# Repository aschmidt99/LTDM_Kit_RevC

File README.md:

# LTDM Kit Rev C

Firmware and hardware assets for a Teensy 4.1 based LTDM (Lorentz Time-Domain Multiplex) kit.

### Programming
Iterate quickly on dsp and string behavior in `Code/LTDM_Kit/render.cpp`, leaving precise timing of sensing and actuating untouched by user.
### Interaction
Map hardware controls (buttons/sliders/pedals) to your algorithm through the UI layer.

## Project Structure

- `Code/LTDM_Kit`: Firmware running on Teensy 4.1
- `Code/Python`: capture, analysis, and Audacity automation scripts
- `Code/LTDM_Kit_Control.maxpat`: a maxpatch for overriding the LTDM Kit physical UI or running LTDM kit main board without UI.
- `Electronics`: KiCad project (schematic and pcb) for PCB design
- `CAD`: mechanical STEP/STL assets for enclosure

## Program and Upload
Firmware can be edited and uploaded to the teensy 4.1 via the Arduino 2.X IDE or from VS code.

### Arduino IDE
To use the Arduino IDE, you will need to [(install the Arduino IDE)](https://support.arduino.cc/hc/en-us/articles/360019833020-Download-and-install-Arduino-IDE). Once installed, download the Teensy Board library by following the instructions [(here)](https://www.pjrc.com/teensy/td_download.html).

After firmware changes are made, make sure the teensy is connected and seen by the dropdown menu in the upper left of the IDE. Use the 'upload' button next to this to flash new firmware.

### Arduino CLI (direct)
If this is your first time connecting from a new machine, run this one-time setup first:

1. Install Arduino CLI.
2. Add the Teensy board index URL.
3. Update board indexes and install the Teensy core.
4. Plug in Teensy 4.1 with a data-capable USB cable.
5. Verify the detected USB port before upload.

Example one-time setup commands:

```bash
# Add PJRC Teensy package index (safe to run again if already present)
arduino-cli config add board_manager.additional_urls https://www.pjrc.com/teensy/package_teensy_index.json

# Refresh indexes and install Teensy core
arduino-cli core update-index
arduino-cli core install teensy:avr

# Confirm Teensy core is installed
arduino-cli core list
```

Check that your Teensy is visible and note its port:

```bash
arduino-cli board list
```

On macOS, Teensy ports commonly look like `/dev/cu.usbmodem*`.

To flash code directly from terminal:

```bash
cd Code/LTDM_Kit
arduino-cli compile --fqbn teensy:avr:teensy41 .
arduino-cli upload --fqbn teensy:avr:teensy41 -p /dev/cu.usbmodemXXXX .
```

### VS Code tasks
To flash firmware from VS code, you can use the premade VS code tasks by using `Cmd+Shift+P` -> `Tasks: Run Task` and select:

- `Teensy: Compile LTDM_Kit`
- `Teensy: Upload LTDM_Kit (prompt port)`
- `Teensy: Upload LTDM_Kit (auto port)`
- `Teensy: Compile + Upload LTDM_Kit (auto port)`

Task definitions live in `.vscode/tasks.json`.

## How the Firmware is Organized

### Essential core files (base firmware)

- `LTDM_Kit.ino`: startup order and top-level loop (`setup()` and `loop()`).
- `flexpwm.cpp` / `flexpwm.h`: hardware timing, ISR, ADC reads, and PWM update path.
- `render.cpp` / `render.h`: per-sample behavior, where algorithm/control logic is authored.
- `ui.cpp` / `ui.h`: physical control scan (buttons/sliders/pedals), LED updates, and serial telemetry printout.
- `channel.h`: per-channel runtime/state struct fields used by ISR and render.
- `context.h`: shared frame context passed into `render()` each sample.
- `pinmap.h`: board pin assignments and hardware routing constants.
- `system_config.h`: global compile-time configuration (sample rate, buffer sizes, PWM resolution).

### Optional or bonus helper modules

These are useful, but not strictly required for a minimal "sense -> render -> actuate" base path.

- `serialctrl.cpp` / `serialctrl.h`: optional host serial override of hardware UI state (used by Max patch control).
- `capture_stream.cpp` / `capture_stream.h`: optional deterministic capture trigger and streaming for measurement scripts.
- `harmonics.cpp` / `harmonics.h`: additive harmonic oscillator bank and zero-crossing pitch tracking.
- `visualAlias.cpp` / `visualAlias.h`: optional visual alias output behavior by plugging a 12V LED strip into one of the channels.
- `SineTable.cpp` / `SineTable.h`: lookup-table sine source used by harmonic/visual helper DSP.
- `debug.h`: compile-time debug print macros (`DEBUG_PRINT`, `DEBUG_PRINTLN`).

At runtime, the flow is:

1. ISR acquires channel state and UI state into `context`.
2. `render(context)` computes output values once per sample.
3. PWM/sense outputs are driven from those computed values.

## Codebase division-of-labor

This codebase intentionally separates three concerns:

1. Real-time infrastructure: sample timing, GPIO/PWM scheduling, ADC/sense capture.
2. Control surface: what knobs/buttons/pedals currently mean.
3. Algorithm: how measured input becomes actuation output.

The design goal is to let you iterate and develop actuation and feedback behavior without destabilizing anything with critical timing, such as the regular periodic sense + actuate loop.

In practice, treat `render.cpp` as your sandbox for algorithmic ideas:

- Feedback shaping
- Noise injection and excitation strategies
- RMS/energy targeting
- Harmonic synthesis
- Cross-channel coupling experiments

## Where to Make Changes

### Audio/actuation behavior

Edit `Code/LTDM_Kit/render.cpp`.

Key entry points:

- `bool renderSetup(LorentzContext *context)` for one-time setup
- `void render(LorentzContext *context)` for per-sample behavior

Useful signals available from `context`:

- `context->ch[0].in`, `context->ch[1].in` (channel's sensed audio input)
- `context->buttons[0]` (button 0-7 are the latching buttons, and 6-15 are the momentary push buttons)
- `context->sliders[0..15]` (slider 0-7 are the potentiometers, 8-15 are the sliders)
- `context->pedals[0..1]` (optionally connect up to 2 expression pedals)

### Button/slider behavior mapping

Edit `Code/LTDM_Kit/ui.cpp` and `Code/LTDM_Kit/render.cpp` together.

How it works:

1. `ui.cpp` scans physical mux inputs and sets UI LED outputs.
2. `render.cpp` assigns meaning to those logical indices.

### Pin assignments

Edit `Code/LTDM_Kit/pinmap.h` only if attaching additional functions to the available GPIOs.

### Render/control behavior (channel 1 focused)

In `Code/LTDM_Kit/render.cpp`:

- Button 0/1 enables channel 1 and 2 output respectively (`enablePin` high/low).
- Button 2 toggles RMS-targeted gain behavior for CH1.
- Button 6 gates CH1 noise injection.
- Button 8 requests capture start while capture is armed.

- Slider 0: CH1 feedback gain (`fbGain`).
- Slider 1: CH1 target RMS.
- Slider 2: noise update rate (acts like coarse smoothing on random term).
- Slider 3: CH1 noise scale.
- Slider 4: harmonic frequency smoothing parameter (`alpha`).
- Sliders 8..15: gains for harmonics 1..8 (`NUM_HARMONICS = 8`).

- Note: Channel 2 currently carries visual-alias pulse output behavior (`renderLEDPulse(...)`) rather than string feedback behavior

### LED/UI feedback

In `Code/LTDM_Kit/ui.cpp`:

- TLC5947 LEDs reflect enable/limit/target and measured RMS states.
- UI scan runs in two-step mux read/write cycles.
- `output()` also prints debug telemetry over serial every ~100 ms (as long as the the python audio capture stream is idle.)

### Serial override mode

`Code/LTDM_Kit/serialctrl.cpp` can override hardware controls via framed serial packets. There is an example max/msp patch ('LTDM_Kit_Control.maxpat') that already has this setup.

- Start marker: `255`
- End marker: `254`
- Payload: mode + 16 sliders + 16 buttons + 2 pedals (34 bytes)

When override is active, incoming values are written directly into the shared UI state arrays.

## Python Tools

The Python tools in `Code/Python` are used for measurement, capture automation, and analysis around the firmware:

- `capture_teensy_plus_interface.py`: Capture audio directly from Teensy (what the teensy 'hears' from the EMF sensing circuitry) and 2 channels of audio from a connected audio interface. Optionally import these files directly to audacity.
- `run_trial.py`: Prompt for trial/profile/duration and launch the capture workflow via named profiles.
- `capture_teensy_stream.py`: Capture Teensy stream only (without interface capture), with optional WAV export.
- `rigol_capture.py`: Run Rigol DS1054Z waveform/screenshot capture and write trial metadata.
- `load_rigol_capture.py`: Load and interactively inspect saved Rigol capture files.
- `rigol_screen.py`: Capture or convert Rigol's screen images.
- `plot_teensy_stream.py`: Plot saved Teensy stream files for quick signal inspection.

If you are starting from scratch, run this script first:

- `Code/Python/run_trial.py`

It prompts for trial and duration, auto-suggests the next trial number, and launches the full capture pipeline with known-good defaults.

Full Python docs:

- `Code/Python/PYTHON_README.md`

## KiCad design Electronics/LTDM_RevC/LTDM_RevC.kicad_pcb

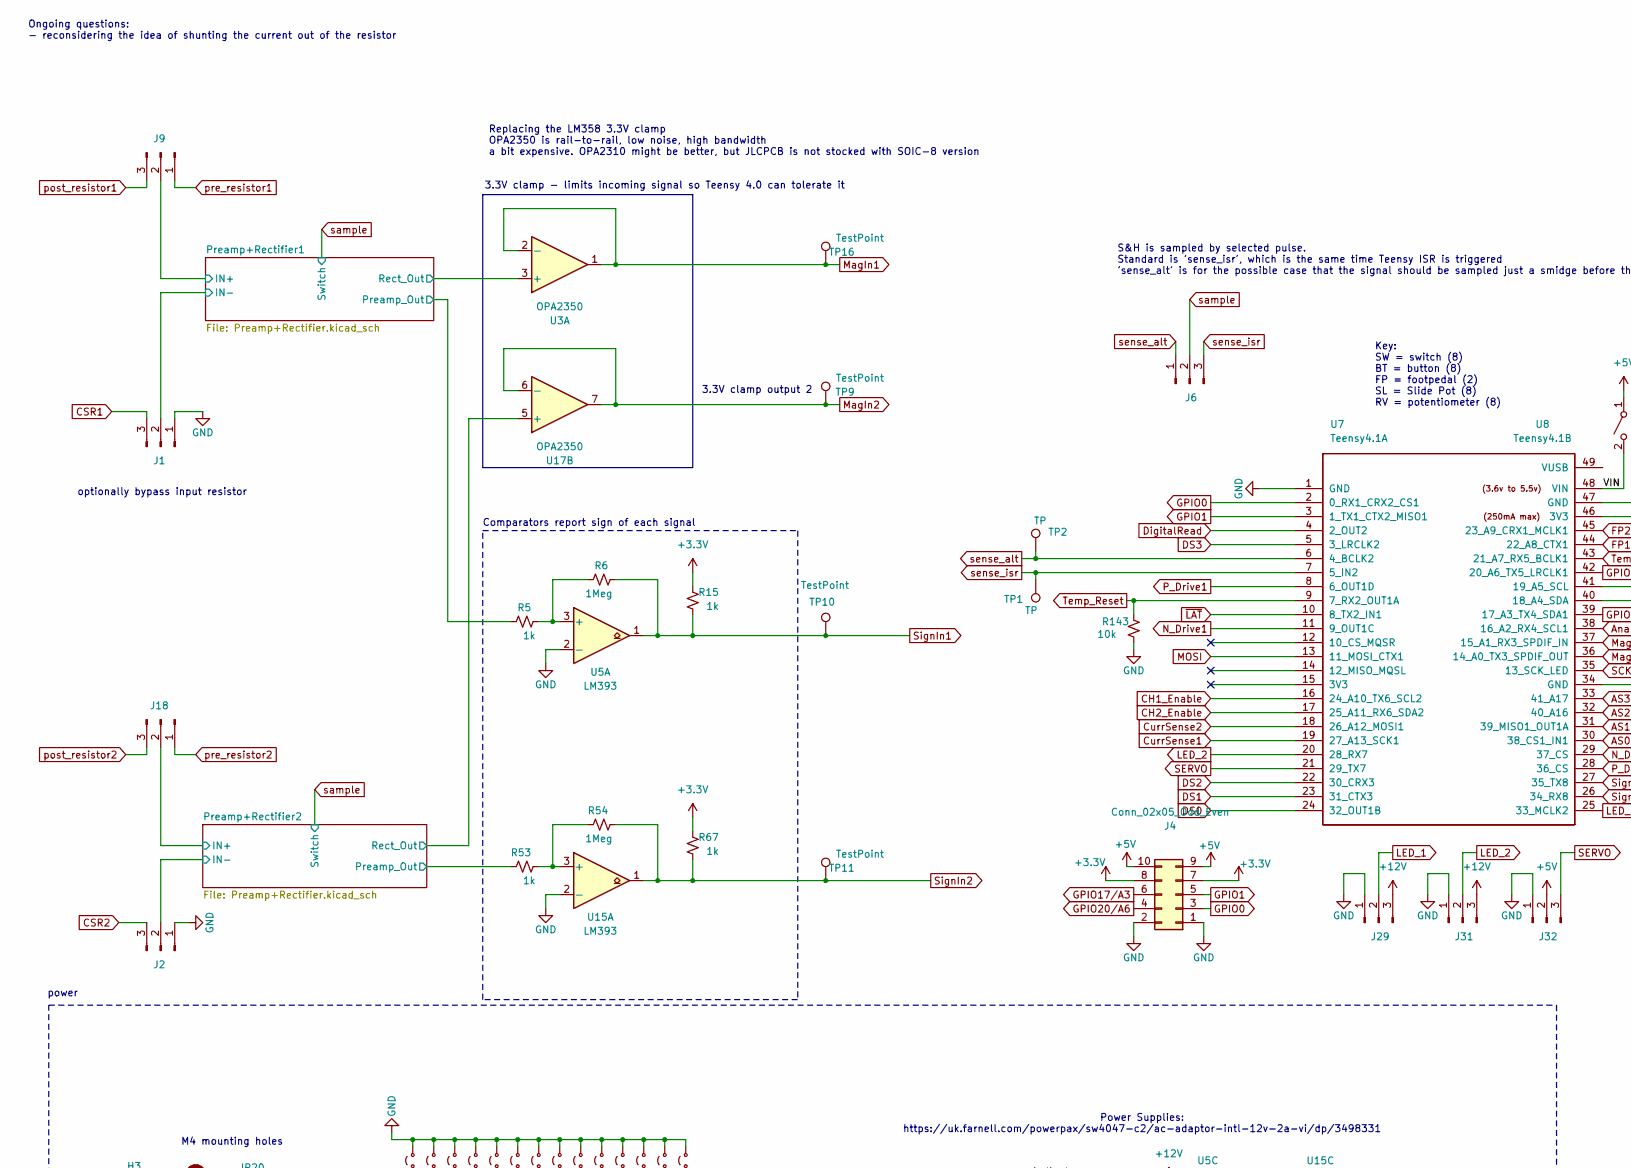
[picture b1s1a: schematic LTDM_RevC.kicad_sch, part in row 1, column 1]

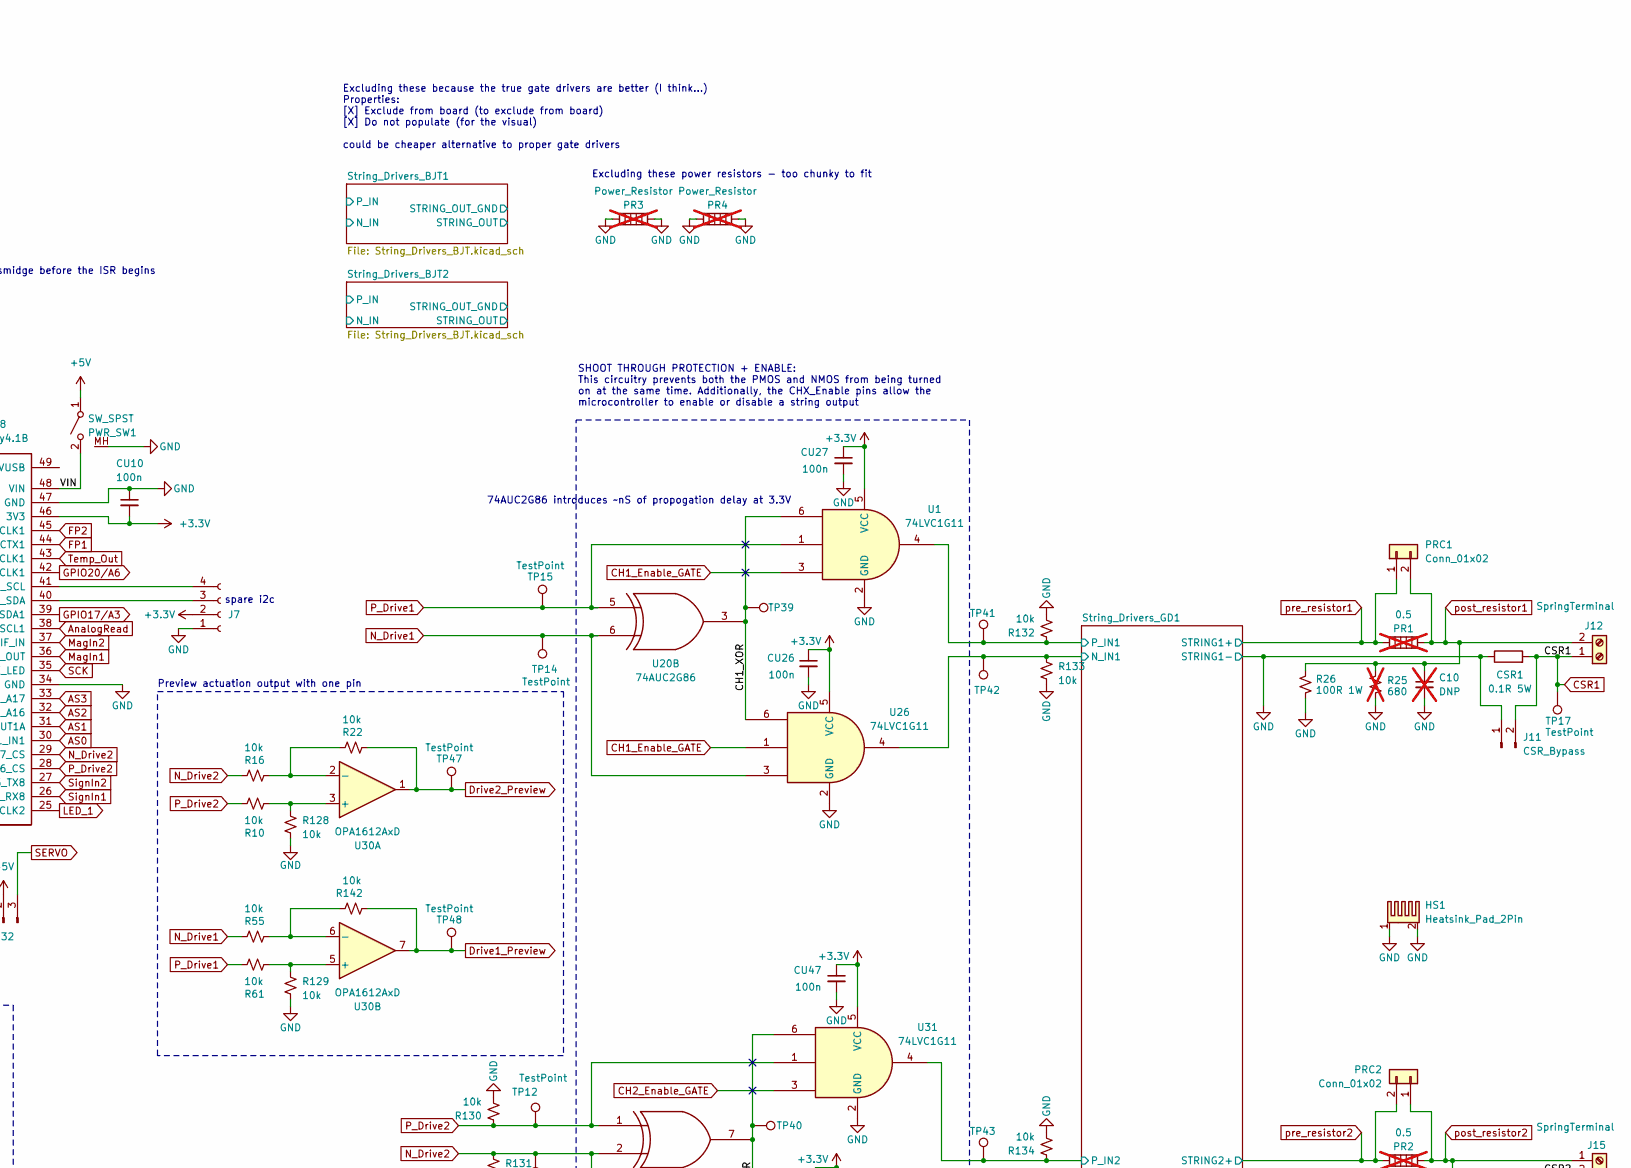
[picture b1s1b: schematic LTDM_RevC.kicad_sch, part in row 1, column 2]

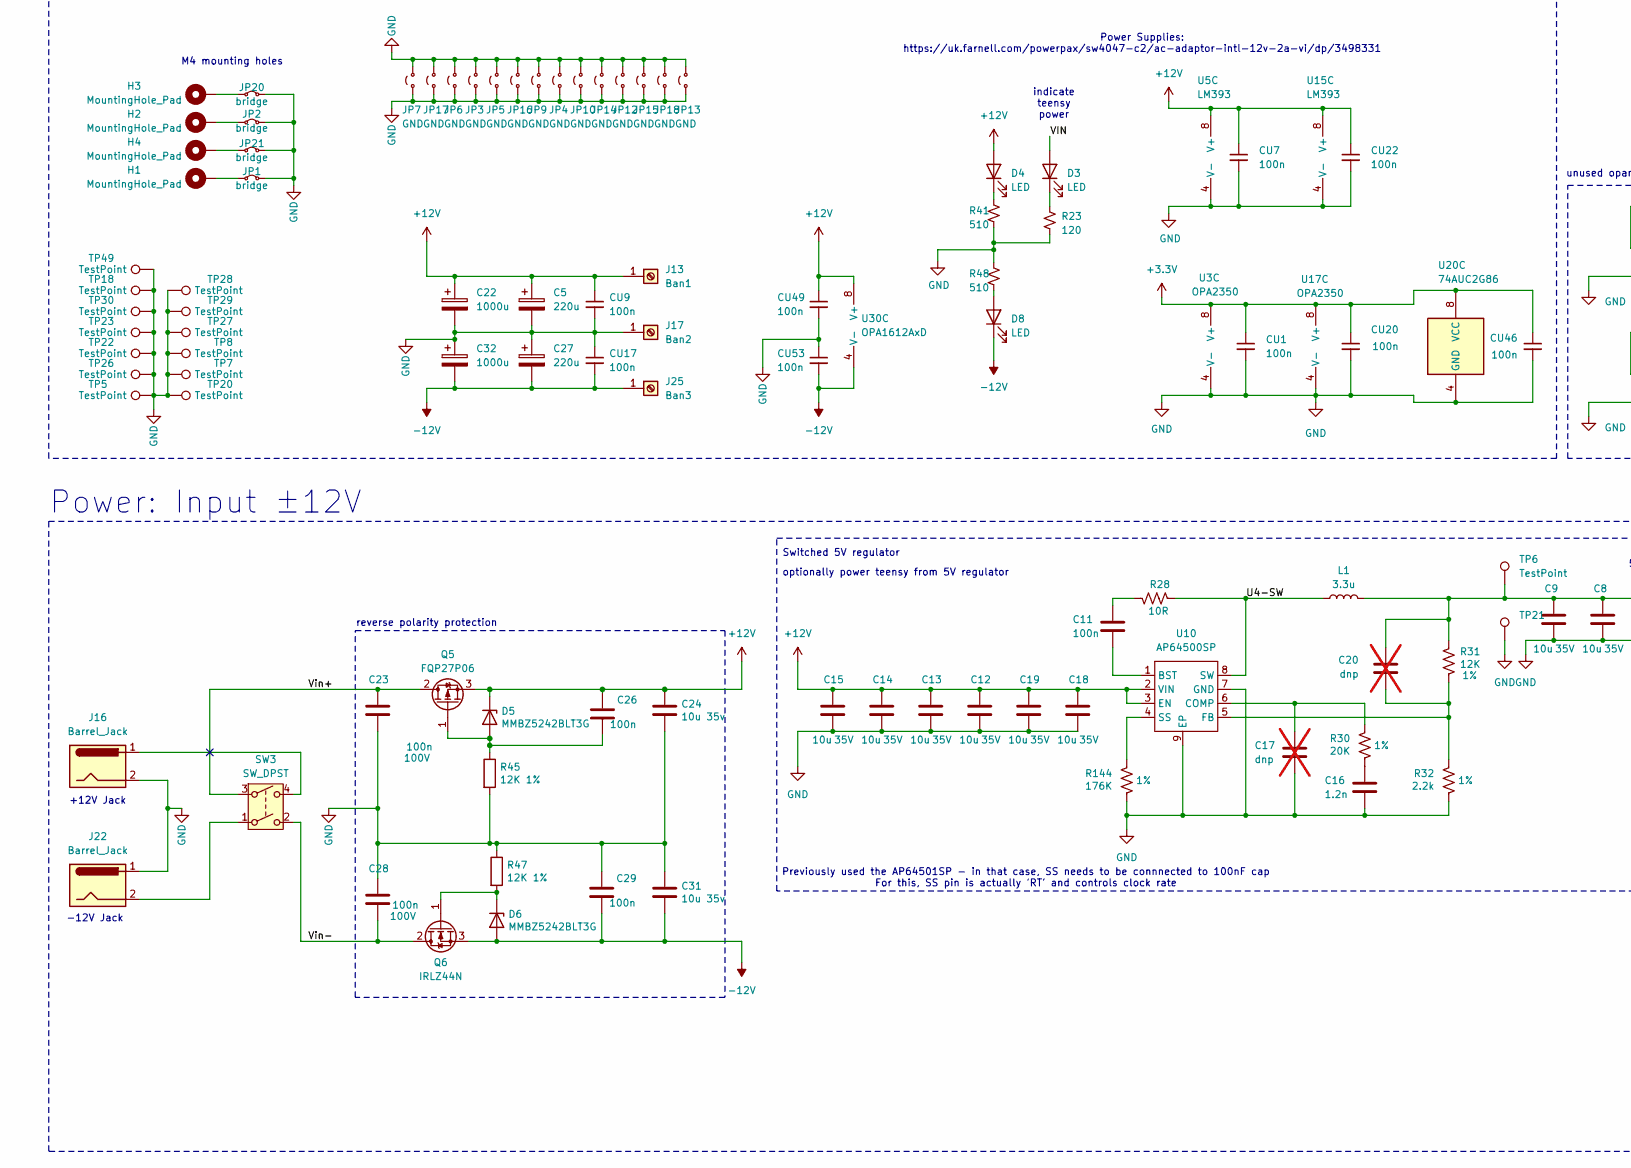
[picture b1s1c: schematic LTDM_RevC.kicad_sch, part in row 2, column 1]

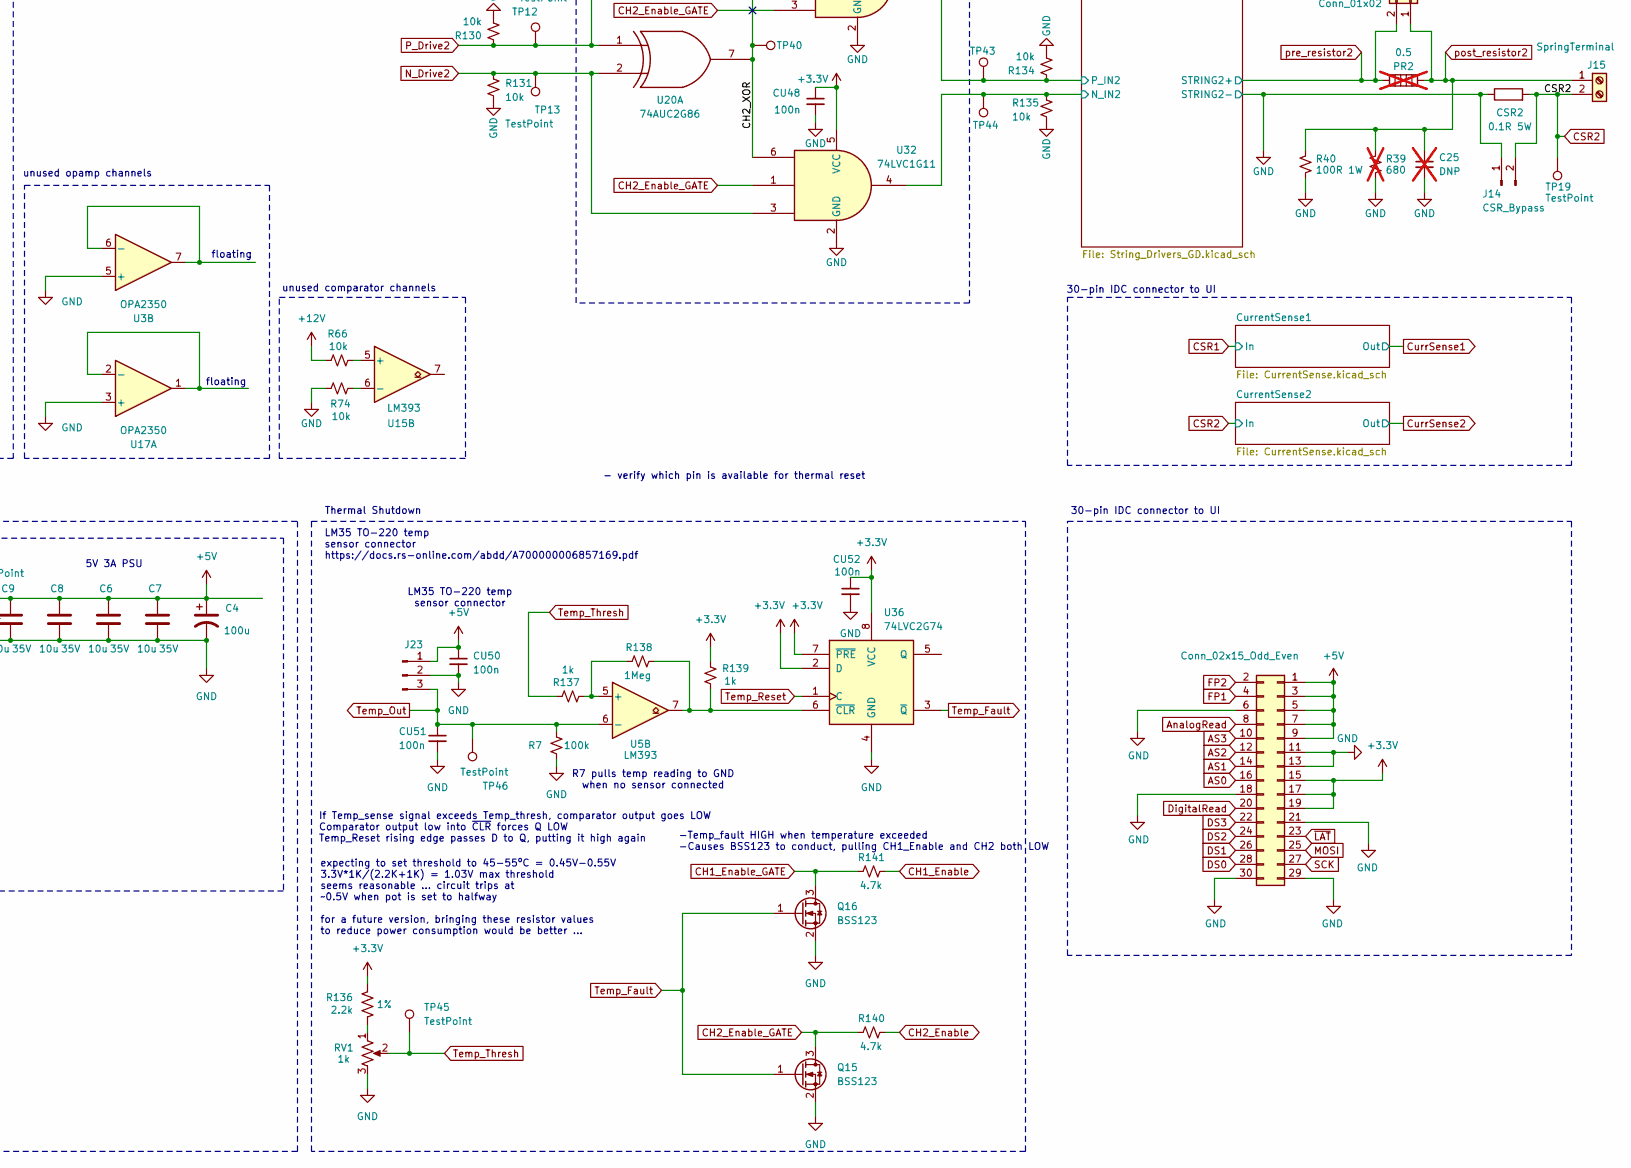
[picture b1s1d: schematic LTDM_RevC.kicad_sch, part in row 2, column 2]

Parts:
C4: 100u; CP_EIA-7343-31_Kemet-D; LCSC C189619
C5, C27: 220u; CP_Radial_D8.0mm_P3.50mm; LCSC C45072
C6, C7, C8, C9: 10u; C_0805_2012Metric; rating 35V; LCSC C117956
C10, C25: DNP; C_Disc_D3.0mm_W1.6mm_P2.50mm; not fitted
C11: 100n; C_0402_1005Metric
C12, C13, C14, C15, C18, C19: 10u; C_0805_2012Metric; rating 35V; LCSC C469541
C16: 1.2n; C_0402_1005Metric
C17, C20: dnp; C_0402_1005Metric; not fitted
C22, C32: 1000u; CP_Radial_D10.0mm_P5.00mm; LCSC C2960265
C23, C28: 100n; C_0402_1005Metric; rating 100V; LCSC C162179
C24, C31: 10u 35v; C_0805_2012Metric; Part Description 10uF 10% or 20% 35V Ceramic Capacitor X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; LCSC C469541
C26, C29: 100n; C_0402_1005Metric; Part Description 0.1uF 10% 16V Ceramic Capacitor X7R 040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; LCSC C92753
CSR1, CSR2: 0.1R 5W; R_4527; LCSC C5127890
CU1, CU7, CU9, CU10, CU17, CU20, CU22, CU26, CU27, CU46, CU47, CU48, CU49, CU50, CU51, CU52, CU53: 100n; C_0603_1608Metric
D3, D4, D8: LED; LED_0603_1608Metric; LCSC C79636
D5, D6: MMBZ5242BLT3G; SOT-23; Part Description Zener Diode 12V 225mW 5% Surface Mount 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; LCSC C896784
H1, H2, H3, H4: MountingHole_Pad; MountingHole_4.3mm_M4_ISO14580_Pad
HS1: Heatsink_Pad_2Pin; Heatsink_Fischer_SK104-STCB_35x13mm__2xDrill3.5mm_ScrewM3
J1, J2, J6, J9, J18, J23, J29, J31, J32: Conn_01x03_Male; PinHeader_1x03_P2.54mm_Vertical; LCSC C2914353
J4: Conn_02x05_Odd_Even; PinHeader_2x05_P2.54mm_Vertical; LCSC C115170
J5: Conn_02x15_Odd_Even; IDC-Header_2x15_P2.54mm_Vertical; LCSC C358748
J7: Conn_01x04_Socket; PinHeader_1x04_P2.54mm_Vertical
J11, J14: CSR_Bypass; SolderJumper-2_P1.3mm_Open_Pad1.0x1.5mm; LCSC C124375
J12, J15: SpringTerminal; TerminalBlock_Spring_2_P5.08mm; LCSC C35616
J13: Ban1; Banana_Jack_1Pin
J16, J22: Barrel_Jack; BarrelJack_Wuerth_6941xx301002; LCSC C3096082
J17: Ban2; Banana_Jack_1Pin
J25: Ban3; Banana_Jack_1Pin
JP1, JP2, JP20, JP21: bridge; SolderJumper-2_P1.3mm_Bridged_RoundedPad1.0x1.5mm
JP3, JP4, JP5, JP6, JP7, JP9, JP10, JP12, JP13, JP14, JP15, JP16, JP17, JP18: GND; SolderJumper-2_subtle
L1: 3.3u; L_Bourns_SRN6045TA; LCSC C3221229
PR1, PR2: 0.5; TO-220-2_Vertical; not fitted
PR3, PR4: Power_Resistor; R_Axial_Power_AluminumCase_AmazonSpecial; not fitted
PRC1, PRC2: Conn_01x02; TerminalBlock_RND_205-00232_1x02_P5.08mm_Horizontal; LCSC C430601
PWR_SW1: SW_SPST; SW_Slide_1P2T_CK_OS102011MS2Q; LCSC C431547
Q5: FQP27P06; TO-220-3_Vertical; LCSC C7503194
Q6: IRLZ44N; TO-220-3_Vertical; LCSC C22367197
Q15, Q16: BSS123; SOT-23; LCSC C78962
R5, R15, R53, R67, R137, R139: 1k; R_0603_1608Metric
R6, R54, R138: 1Meg; R_0603_1608Metric
R7: 100k; R_0603_1608Metric
R10, R16, R22, R55, R61, R66, R74, R128, R129, R130, R131, R132, R133, R134, R135, R142, R143: 10k; R_0603_1608Metric
R23: 120; R_0603_1608Metric
R25, R39: 680; R_Axial_DIN0207_L6.3mm_D2.5mm_P10.16mm_Horizontal; not fitted
R26, R40: 100R 1W; R_2512_6332Metric; LCSC C24920
R28: 10R; R_0402_1005Metric; LCSC C138066
R30: 20K; R_0402_1005Metric; tolerance 1%
R31: 12K; R_0402_1005Metric; tolerance 1%; LCSC C25752
R32: 2.2k; R_0402_1005Metric; tolerance 1%
R41, R48: 510; R_0603_1608Metric; LCSC C309660
R45, R47: 12K 1%; R_0402_1005Metric; Part Description Resistor 12K M1005 1% 63mW; LCSC C25535
R136: 2.2k; R_0603_1608Metric; tolerance 1%
R140, R141: 4.7k; R_0603_1608Metric
R144: 176K; R_0402_1005Metric; tolerance 1%; LCSC C862921
RV1: 1k; Potentiometer_Bourns_3314G_Vertical; LCSC C780221
SW3: SW_DPST; PinHeader_2x02_P2.54mm_Vertical; LCSC C5272597
TP1, TP2: TP; TestPoint_THTPad_D2.0mm_Drill1.0mm
TP5, TP7, TP8, TP18, TP20, TP22, TP23, TP26, TP27, TP28, TP29, TP30, TP49: TestPoint; TestPoint_THTPad_D2.0mm_Drill1.0mm; LCSC C238127
TP6, TP9, TP10, TP11, TP12, TP13, TP14, TP15, TP16, TP17, TP19, TP21, TP39, TP40, TP41, TP42, TP43, TP44, TP45, TP46, TP47, TP48: TestPoint; TestPoint_THTPad_D2.0mm_Drill1.0mm; LCSC C238122
U1, U26, U31, U32: 74LVC1G11; SOT-23-6; LCSC C22356918
U3, U17: OPA2350; SOP-8_3.76x4.96mm_P1.27mm; LCSC C55904
U5, U15: LM393; SOP-8_3.76x4.96mm_P1.27mm; LCSC C7955
U7: Teensy4.1A; LCSC C41376163
U8: Teensy4.1B; LCSC C41376163
U10: AP64500SP; SOIC-8-1EP_3.9x4.9mm_P1.27mm_EP2.95x4.9mm_Mask2.71x3.4mm_Th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; LCSC C2070920
U20: 74AUC2G86; VSSOP-8_2.3x2mm_P0.5mm; LCSC C2876515
U30: OPA1612AxD; SOP-8_3.76x4.96mm_P1.27mm; LCSC C94590
U36: 74LVC2G74; VSSOP-8_2.3x2mm_P0.5mm; LCSC C7851

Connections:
+3.3V: CU1.1, CU10.2, CU20.1, CU26.1, CU27.1, CU46.1, CU47.1, CU48.1, CU52.1, J4.7, J4.8, J5.15, J5.17, J5.19, J7.2, R15.2, R67.2, R136.1, R139.2, U1.5 (VCC), U3.8 (V+), U8.46 (3V3), U17.8 (V+), U20.8 (VCC), U26.5 (VCC), U31.5 (VCC), U32.5 (VCC), U36.2 (D), U36.7 (~PRE), U36.8 (VCC); also elsewhere on the board
+5V: C4.1, C6.1, C7.1, C8.1, C9.1, C20.1, CU50.1, J4.9, J4.10, J5.1, J5.3, J5.5, J5.7, J5.9, J23.1, J32.2, L1.2, PWR_SW1.1 (A), R31.1, TP6.1 (1_1)
+12V: C5.1, C12.1, C13.1, C14.1, C15.1, C18.1, C19.1, C22.1, C24.1, C26.1, CU7.1, CU9.1, CU22.1, CU49.1, D4.2 (A), D5.3 (K), J13.1 (Pin_1_1), J29.3, J31.3, Q5.3 (S), R66.2, U5.8 (V+), U10.2 (VIN), U10.3 (EN), U15.8 (V+), U30.8 (V+); also elsewhere on the board
-12V: C27.2, C29.2, C31.2, C32.2, CU17.2, CU53.2, D6.1 (A), D8.1 (K), J25.1 (Pin_1_1), Q6.3 (S), U30.4 (V-); also elsewhere on the board
/CH1_XOR: TP39.1 (1_1), U1.6, U20.3, U26.6
/CH2_XOR: TP40.1 (1_1), U20.7, U31.6, U32.6
/Preamp+Rectifier1/IN+: J9.2; also elsewhere on the board
/Preamp+Rectifier1/IN-: J1.2; also elsewhere on the board
/Preamp+Rectifier1/Rect_Out: U3.3 (+); also elsewhere on the board
/Preamp+Rectifier1/rect_in: R5.1; also elsewhere on the board
/Preamp+Rectifier2/IN+: J18.2; also elsewhere on the board
/Preamp+Rectifier2/IN-: J2.2; also elsewhere on the board
/Preamp+Rectifier2/Rect_Out: U17.5 (+); also elsewhere on the board
/Preamp+Rectifier2/rect_in: R53.1; also elsewhere on the board
/String_Drivers_GD1/N_IN1: R133.2, TP42.1 (1_1), U26.4; also elsewhere on the board
/String_Drivers_GD1/N_IN2: R135.2, TP44.1 (1_1), U32.4; also elsewhere on the board
/String_Drivers_GD1/P_IN1: R132.2, TP41.1 (1_1), U1.4; also elsewhere on the board
/String_Drivers_GD1/P_IN2: R134.2, TP43.1 (1_1), U31.4; also elsewhere on the board
/U4-SW: L1.1, R28.1, U10.8 (SW)
/VIN: D3.2 (A), PWR_SW1.2 (B), U8.48 (VIN)
/Vin+: C23.1, Q5.2 (D), SW3.3
/Vin-: C28.2, Q6.2 (D), SW3.2
AS0: J5.16, U8.30 (38_CS1_IN1)
AS1: J5.14, U8.31 (39_MISO1_OUT1A)
AS2: J5.12, U8.32 (40_A16)
AS3: J5.10, U8.33 (41_A17)
AnalogRead: J5.8, U8.38 (16_A2_RX4_SCL1)
CH1_Enable: R141.2, U7.16 (24_A10_TX6_SCL2)
CH1_Enable_GATE: Q16.3 (D), R141.1, U1.3, U26.1
CH2_Enable: R140.2, U7.17 (25_A11_RX6_SDA2)
CH2_Enable_GATE: Q15.3 (D), R140.1, U31.3, U32.1
CSR1: CSR1.2, J1.3, J11.2, J12.1, TP17.1 (1_1); also elsewhere on the board
CSR2: CSR2.2, J2.3, J14.2, J15.2, TP19.1 (1_1); also elsewhere on the board
CurrSense1: U7.19 (27_A13_SCK1); also elsewhere on the board
CurrSense2: U7.18 (26_A12_MOSI1); also elsewhere on the board
DS0: J5.28, U7.24 (32_OUT1B)
DS1: J5.26, U7.23 (31_CTX3)
DS2: J5.24, U7.22 (30_CRX3)
DS3: J5.22, U7.5 (3_LRCLK2)
DigitalRead: J5.20, U7.4 (2_OUT2)
Drive1_Preview: R142.1, TP48.1 (1_1), U30.7
Drive2_Preview: R22.1, TP47.1 (1_1), U30.1
FP1: J5.4, U8.44 (22_A8_CTX1)
FP2: J5.2, U8.45 (23_A9_CRX1_MCLK1)
GND: C4.2, C5.2, C6.2, C7.2, C8.2, C9.2, C10.2, C12.2, C13.2, C14.2, C15.2, C16.2, C17.2, C18.2, C19.2, C22.2, C23.2, C24.2, C25.2, C27.1, C28.1, C29.1, C31.1, C32.1, CSR1.1, CSR2.1, CU1.2, CU7.2, CU9.2, CU10.1, CU17.1, CU20.2, CU22.2, CU26.2, CU27.2, CU46.2, CU47.2, CU48.2, CU49.2, CU50.2, CU51.2, CU52.2, CU53.1, HS1.1, HS1.2, J1.1, J2.1, J4.1, J4.2, J5.6, J5.11, J5.13, J5.18, J5.21, J5.29, J5.30, J7.1, J11.1, J14.1, J16.2, J17.1 (Pin_1_1), J22.1, J23.2, J29.1, J31.1, J32.1, JP1.2 (B), JP2.2 (B), JP3.1 (A), JP3.2 (B), JP4.1 (A), JP4.2 (B), JP5.1 (A), JP5.2 (B), JP6.1 (A), JP6.2 (B), JP7.1 (A), JP7.2 (B), JP9.1 (A), JP9.2 (B), JP10.1 (A), JP10.2 (B), JP12.1 (A), JP12.2 (B), JP13.1 (A), JP13.2 (B), JP14.1 (A), JP14.2 (B), JP15.1 (A), JP15.2 (B), JP16.1 (A), JP16.2 (B), JP17.1 (A), JP17.2 (B), JP18.1 (A), JP18.2 (B), JP20.2 (B), JP21.2 (B), PR3.1, PR3.2, PR4.1, PR4.2, PWR_SW1.MH, Q15.2 (S), Q16.2 (S), R7.1, R23.1, R25.1, R26.1, R32.2, R39.1, R40.1, R41.1, R45.2, R47.1, R48.2, R74.2, R128.1, R129.1, R130.1, R131.1, R132.1, R133.1, R134.1, R135.1, R143.1, R144.2, RV1.3, TP5.1 (1_1), TP7.1 (1_1), TP8.1 (1_1), TP18.1 (1_1), TP20.1 (1_1), TP21.1 (1_1), TP22.1 (1_1), TP23.1 (1_1), TP26.1 (1_1), TP27.1 (1_1), TP28.1 (1_1), TP29.1 (1_1), TP30.1 (1_1), TP49.1 (1_1), U1.2 (GND), U3.4 (V-), U3.5 (+), U5.2 (-), U5.4 (V-), U7.1 (GND), U8.34 (GND), U8.47 (GND), U10.7 (GND), U10.9 (EP), U15.2 (-), U15.4 (V-), U17.3 (+), U17.4 (V-), U20.4 (GND), U26.2 (GND), U31.2 (GND), U32.2 (GND), U36.4 (GND); also elsewhere on the board
GPIO0: J4.3, U7.2 (0_RX1_CRX2_CS1)
GPIO1: J4.5, U7.3 (1_TX1_CTX2_MISO1)
GPIO17/A3: J4.6, U8.39 (17_A3_TX4_SDA1)
GPIO20/A6: J4.4, U8.42 (20_A6_TX5_LRCLK1)
LED_1: J29.2, U8.25 (33_MCLK2)
LED_2: J31.2, U7.20 (28_RX7)
MOSI: J5.25, U7.13 (11_MOSI_CTX1)
MagIn1: TP16.1 (1_1), U3.1, U3.2 (-), U8.36 (14_A0_TX3_SPDIF_OUT)
MagIn2: TP9.1 (1_1), U8.37 (15_A1_RX3_SPDIF_IN), U17.6 (-), U17.7
N_Drive1: R55.2, TP14.1 (1_1), U7.11 (9_OUT1C), U20.6, U26.3
N_Drive2: R16.2, R131.2, TP13.1 (1_1), U8.29 (37_CS), U20.2, U32.3
unnamed: C11.1, R28.2
unnamed: C16.1, R30.2
unnamed: D3.1 (K), R23.2
unnamed: D4.1 (K), R41.2
unnamed: C26.2, D5.1 (A), Q5.1 (G), R45.1
unnamed: D6.3 (K), Q6.1 (G), R47.2
unnamed: D8.2 (A), R48.1
unnamed: J7.3, U8.40 (18_A4_SDA)
unnamed: J7.4, U8.41 (19_A5_SCL)
unnamed: J16.1, SW3.4
unnamed: J22.2, SW3.1
unnamed: H1.1 (1_1), JP1.1 (A)
unnamed: H2.1 (1_1), JP2.1 (A)
unnamed: H3.1 (1_1), JP20.1 (A)
unnamed: H4.1 (1_1), JP21.1 (A)
unnamed: R136.2, RV1.1
unnamed: U3.6 (-), U3.7
unnamed: R5.2, R6.1, U5.3 (+)
unnamed: R137.2, R138.1, U5.5 (+)
unnamed: C11.2, U10.1 (BST)
unnamed: C17.1, R30.1, U10.6 (COMP)
unnamed: C20.2, R31.2, R32.1, U10.5 (FB)
unnamed: R144.1, U10.4 (SS)
unnamed: R53.2, R54.1, U15.3 (+)
unnamed: R66.1, U15.5 (+)
unnamed: R74.1, U15.6 (-)
unnamed: U17.1, U17.2 (-)
unnamed: R10.1, R128.2, U30.3 (+)
unnamed: R16.1, R22.2, U30.2 (-)
unnamed: R61.1, R129.2, U30.5 (+)
unnamed: R55.1, R142.2, U30.6 (-)
unnamed: R138.2, R139.1, U5.7, U36.6 (~CLR)
P_Drive1: R61.2, TP15.1 (1_1), U1.1, U7.8 (6_OUT1D), U20.5
P_Drive2: R10.2, R130.2, TP12.1 (1_1), U8.28 (36_CS), U20.1, U31.1
SCK: J5.27, U8.35 (13_SCK_LED)
SERVO: J32.3, U7.21 (29_TX7)
SignIn1: R6.2, R15.1, TP10.1 (1_1), U5.1, U8.26 (34_RX8)
SignIn2: R54.2, R67.1, TP11.1 (1_1), U8.27 (35_TX8), U15.1
Temp_Fault: Q15.1 (G), Q16.1 (G), U36.3 (~Q)
Temp_Out: CU51.1, J23.3, R7.2, TP46.1 (1_1), U5.6 (-), U8.43 (21_A7_RX5_BCLK1)
Temp_Reset: R143.2, U7.9 (7_RX2_OUT1A), U36.1 (C)
Temp_Thresh: R137.1, RV1.2, TP45.1 (1_1)
post_resistor1: C10.1, J9.3, J12.2, PR1.2, PRC1.2, R25.2, R26.2
post_resistor2: C25.1, J15.1, J18.3, PR2.1, PRC2.1, R39.2, R40.2
pre_resistor1: J9.1, PR1.1, PRC1.1; also elsewhere on the board
pre_resistor2: J18.1, PR2.2, PRC2.2; also elsewhere on the board
sample: J6.2; also elsewhere on the board
sense_alt: J6.1, TP2.1 (1_1), U7.6 (4_BCLK2)
sense_isr: J6.3, TP1.1 (1_1), U7.7 (5_IN2)
~LAT: J5.23, U7.10 (8_TX2_IN1)

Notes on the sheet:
floating
5V 3A PSU
optionally bypass input resistor
Previously used the AP64501SP - in that case, SS needs to be connnected to 100nF cap For this, SS pin is actually 'RT' and controls clock rate
reverse polarity protection
power
Ongoing questions: - reconsidering the idea of shunting the current out of the resistor
3.3V clamp output 2
Replacing the LM358 3.3V clamp OPA2350 is rail-to-rail, low noise, high bandwidth a bit expensive. OPA2310 might be better, but JLCPCB is not stocked with SOIC-8 version
R7 pulls temp reading to GND when no sensor connected
indicate teensy power
SHOOT THROUGH PROTECTION + ENABLE: This circuitry prevents both the PMOS and NMOS from being turned on at the same time. Additionally, the CHX_Enable pins allow the microcontroller to enable or disable a string output
Power: Input ±12V
optionally power teensy from 5V regulator
If Temp_sense signal exceeds Temp_thresh, comparator output goes LOW Comparator output low into ~{CLR} forces Q LOW Temp_Reset rising edge passes D to Q, putting it high again
- verify which pin is available for thermal reset
Key: SW = switch (8) BT = button (8) FP = footpedal (2) SL = Slide Pot (8) RV = potentiometer (8)
+12V Jack
LM35 TO-220 temp sensor connector https://docs.rs-online.com/abdd/A700000006857169.pdf
Power Supplies: https://uk.farnell.com/powerpax/sw4047-c2/ac-adaptor-intl-12v-2a-vi/dp/3498331
74AUC2G86 introduces ~nS of propogation delay at 3.3V
-Temp_fault HIGH when temperature exceeded -Causes BSS123 to conduct, pulling CH1_Enable and CH2 both LOW
Preview actuation output with one pin
30-pin IDC connector to UI
Switched 5V regulator
Thermal Shutdown
-12V Jack
Excluding these power resistors - too chunky to fit
spare i2c
expecting to set threshold to 45-55ºC = 0.45V-0.55V 3.3V*1K/(2.2K+1K) = 1.03V max threshold seems reasonable ... circuit trips at ~0.5V when pot is set to halfway for a future version, bringing these resistor values to reduce power consumption would be better ...
Excluding these because the true gate drivers are better (I think...) Properties: [X] Exclude from board (to exclude from board) [X] Do not populate (for the visual) could be cheaper alternative to proper gate drivers
unused opamp channels
LM35 TO-220 temp sensor connector
3.3V clamp - limits incoming signal so Teensy 4.0 can tolerate it
M4 mounting holes
unused comparator channels
S&H is sampled by selected pulse. Standard is 'sense_isr', which is the same time Teensy ISR is triggered 'sense_alt' is for the possible case that the signal should be sampled just a smidge before the ISR begins
Comparators report sign of each signal

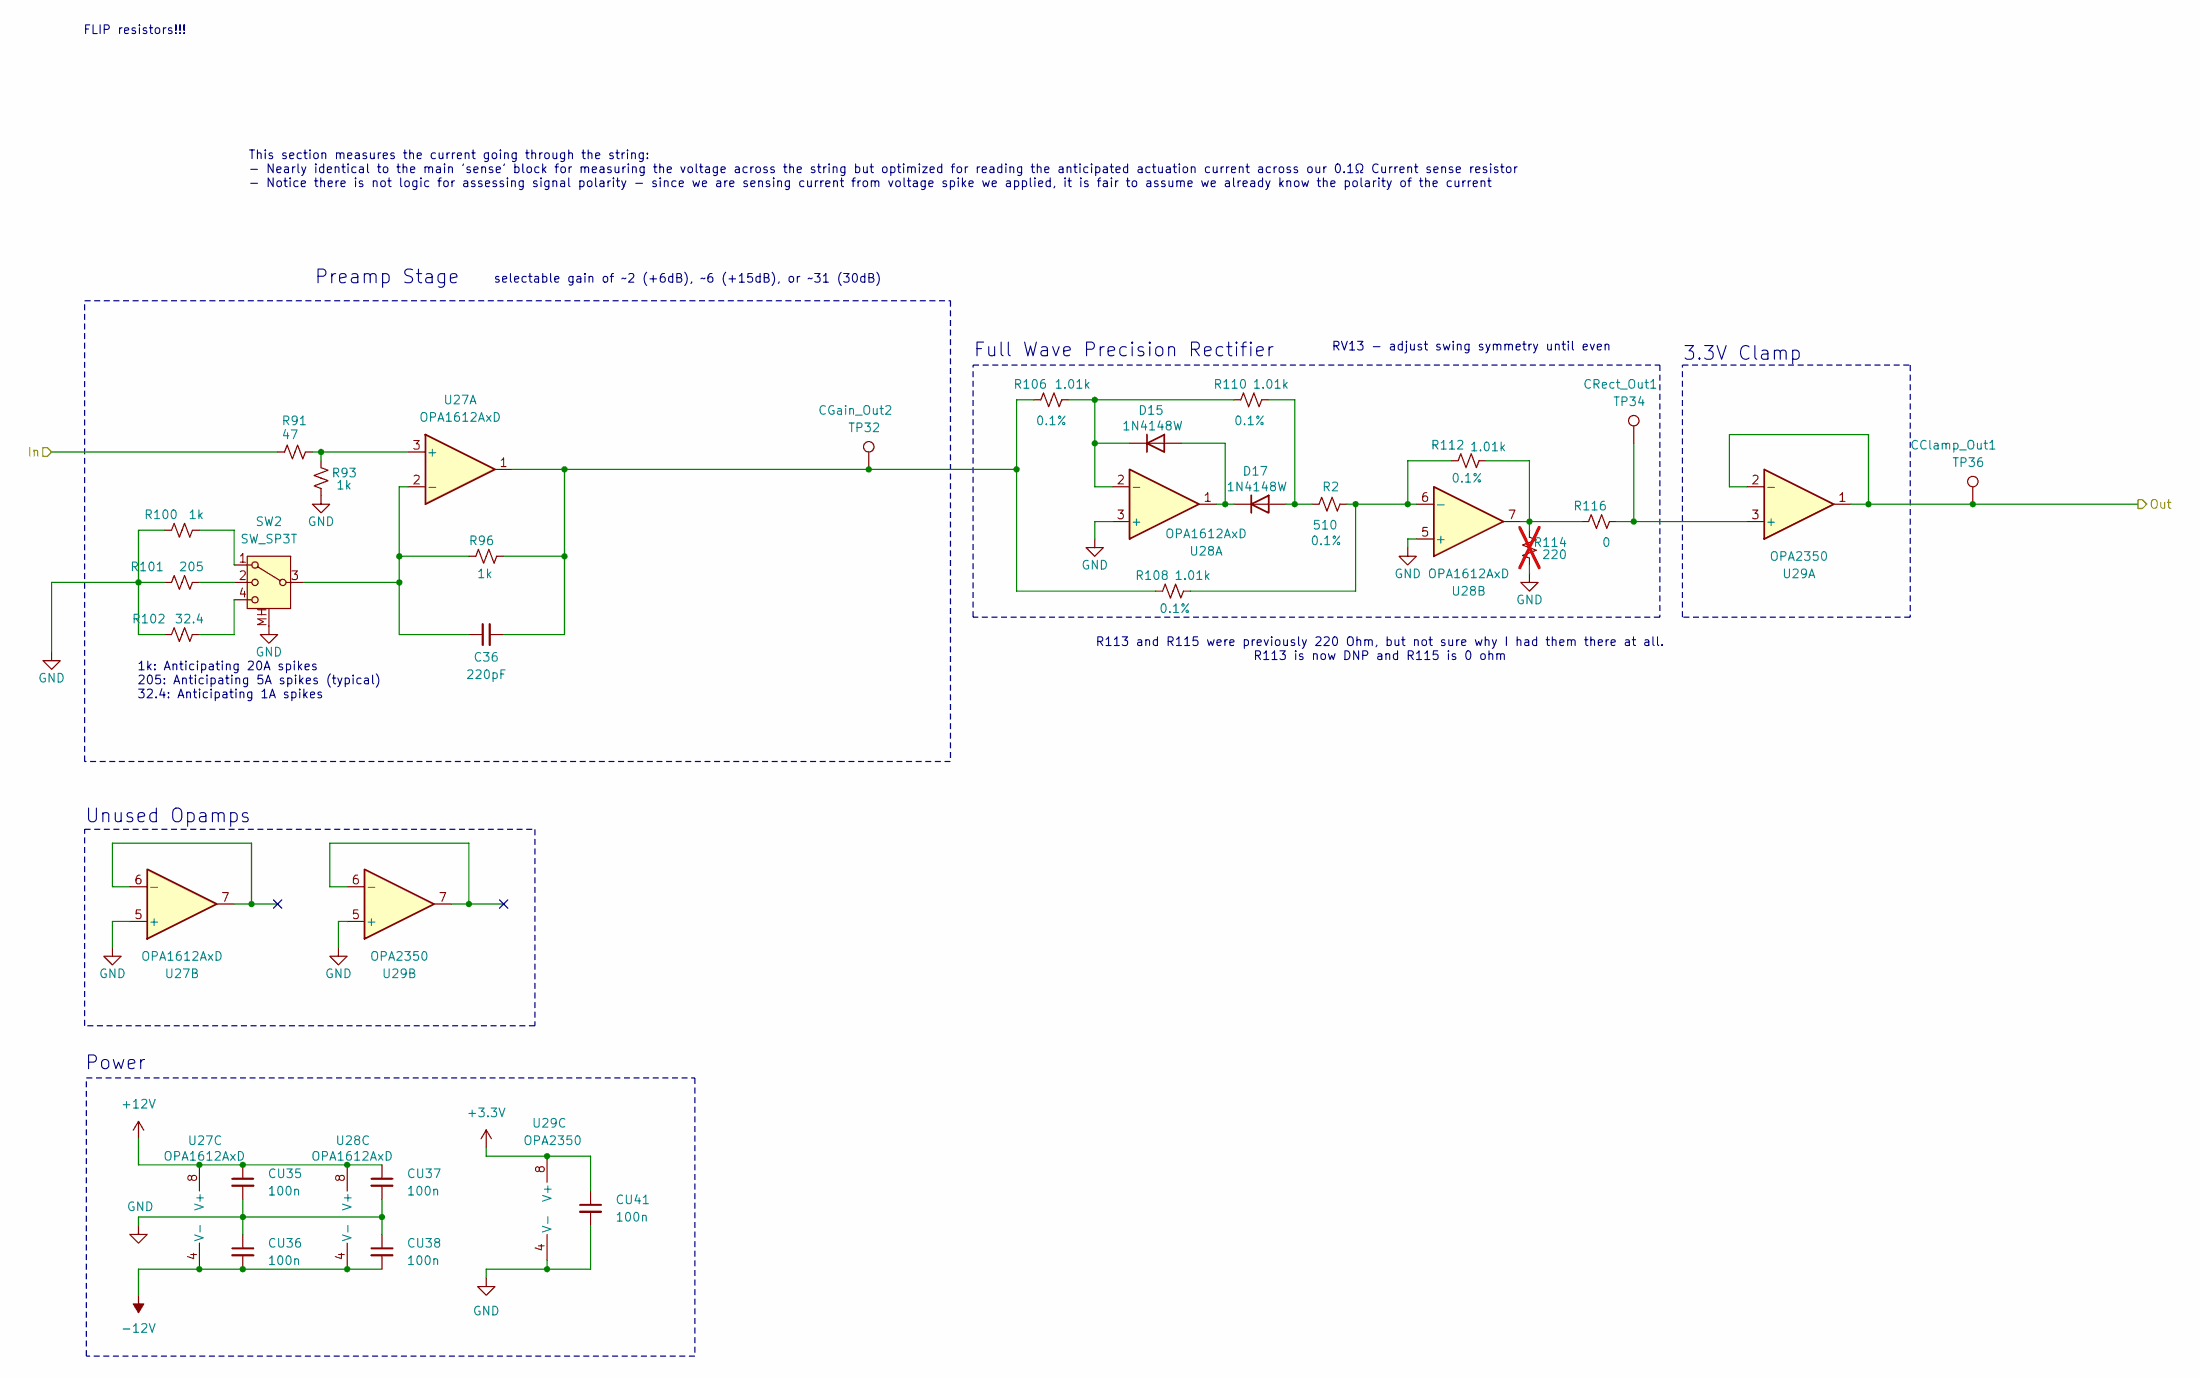
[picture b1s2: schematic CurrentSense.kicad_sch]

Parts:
C36: 220pF; C_0603_1608Metric
CU35, CU36, CU37, CU38, CU41: 100n; C_0603_1608Metric
D15, D17: 1N4148W; D_SOD-123; LCSC C5345962
R2: 510; R_0603_1608Metric; LCSC C309660
R91: 47; R_0603_1608Metric
R93, R96, R100: 1k; R_0603_1608Metric
R101: 205; R_0603_1608Metric; LCSC C403059
R102: 32.4; R_0603_1608Metric; LCSC C861326
R106, R108, R110, R112: 1.01k; R_0603_1608Metric; LCSC C861188
R114: 220; R_0603_1608Metric; not fitted
R116: 0; R_0603_1608Metric
SW2: SW_SP3T; SW_Slide-SSSS918700; LCSC C390919
TP32: CGain_Out2; TestPoint_THTPad_D2.0mm_Drill1.0mm; LCSC C238122
TP34: CRect_Out1; TestPoint_THTPad_D2.0mm_Drill1.0mm; LCSC C238122
TP36: CClamp_Out1; TestPoint_THTPad_D2.0mm_Drill1.0mm; LCSC C238122
U27, U28: OPA1612AxD; SOP-8_3.76x4.96mm_P1.27mm; LCSC C94590
U29: OPA2350; SOP-8_3.76x4.96mm_P1.27mm; LCSC C55904

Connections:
+3.3V: CU41.1, U29.8 (V+); also elsewhere on the board
+12V: CU35.1, CU37.1, U27.8 (V+), U28.8 (V+); also elsewhere on the board
-12V: CU36.2, CU38.2, U27.4 (V-), U28.4 (V-); also elsewhere on the board
CSR2: R91.2; also elsewhere on the board
CurrSense2: TP36.1 (1_1), U29.1, U29.2 (-); also elsewhere on the board
GND: CU35.2, CU36.1, CU37.2, CU38.1, CU41.2, R93.1, R100.1, R101.1, R102.1, R114.1, SW2.MH, U27.5 (+), U28.3 (+), U28.5 (+), U29.4 (V-), U29.5 (+); also elsewhere on the board
unnamed: C36.2, R96.2, R106.1, R108.1, TP32.1 (1_1), U27.1
unnamed: D15.2 (A), D17.1 (K), U28.1
unnamed: D15.1 (K), R106.2, R110.1, U28.2 (-)
unnamed: D17.2 (A), R2.1, R110.2
unnamed: R100.2, SW2.1
unnamed: R101.2, SW2.2
unnamed: R102.2, SW2.4
unnamed: R112.2, R114.2, R116.1, U28.7
unnamed: R91.1, R93.2, U27.3 (+)
unnamed: C36.1, R96.1, SW2.3, U27.2 (-)
unnamed: R2.2, R108.2, R112.1, U28.6 (-)
unnamed: R116.2, TP34.1 (1_1), U29.3 (+)

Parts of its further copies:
C35: 220pF; C_0603_1608Metric
CU28, CU29, CU30, CU31, CU34: 100n; C_0603_1608Metric
D14, D16: 1N4148W; D_SOD-123; LCSC C5345962
R50: 510; R_0603_1608Metric; LCSC C309660
R90: 47; R_0603_1608Metric
R92, R95, R97: 1k; R_0603_1608Metric
R98: 205; R_0603_1608Metric; LCSC C403059
R99: 32.4; R_0603_1608Metric; LCSC C861326
R105, R107, R109, R111: 1.01k; R_0603_1608Metric; LCSC C861188
R113: 220; R_0603_1608Metric; not fitted
R115: 0; R_0603_1608Metric
SW1: SW_SP3T; SW_Slide-SSSS918700; LCSC C390919
TP31: CGain_Out2; TestPoint_THTPad_D2.0mm_Drill1.0mm; LCSC C238122
TP33: CRect_Out1; TestPoint_THTPad_D2.0mm_Drill1.0mm; LCSC C238122
TP35: CClamp_Out1; TestPoint_THTPad_D2.0mm_Drill1.0mm; LCSC C238122
U18, U19: OPA1612AxD; SOP-8_3.76x4.96mm_P1.27mm; LCSC C94590
U21: OPA2350; SOP-8_3.76x4.96mm_P1.27mm; LCSC C55904

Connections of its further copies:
+3.3V: CU34.1, U21.8 (V+); also elsewhere on the board
+12V: CU28.1, CU30.1, U18.8 (V+), U19.8 (V+); also elsewhere on the board
-12V: CU29.2, CU31.2, U18.4 (V-), U19.4 (V-); also elsewhere on the board
CSR1: R90.2; also elsewhere on the board
CurrSense1: TP35.1 (1_1), U21.1, U21.2 (-); also elsewhere on the board
GND: CU28.2, CU29.1, CU30.2, CU31.1, CU34.2, R92.1, R97.1, R98.1, R99.1, R113.1, SW1.MH, U18.5 (+), U19.3 (+), U19.5 (+), U21.4 (V-), U21.5 (+); also elsewhere on the board
unnamed: C35.2, R95.2, R105.1, R107.1, TP31.1 (1_1), U18.1
unnamed: D14.2 (A), D16.1 (K), U19.1
unnamed: D14.1 (K), R105.2, R109.1, U19.2 (-)
unnamed: D16.2 (A), R50.1, R109.2
unnamed: R97.2, SW1.1
unnamed: R98.2, SW1.2
unnamed: R99.2, SW1.4
unnamed: R111.2, R113.2, R115.1, U19.7
unnamed: R90.1, R92.2, U18.3 (+)
unnamed: C35.1, R95.1, SW1.3, U18.2 (-)
unnamed: R50.2, R107.2, R111.1, U19.6 (-)
unnamed: R115.2, TP33.1 (1_1), U21.3 (+)

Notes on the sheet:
This section measures the current going through the string: - Nearly identical to the main 'sense' block for measuring the voltage across the string but optimized for reading the anticipated actuation current across our 0.1Ω Current sense resistor - Notice there is not logic for assessing signal po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
selectable gain of ~2 (+6dB), ~6 (+15dB), or ~31 (30dB)
RV13 - adjust swing symmetry until even
Full Wave Precision Rectifier
Unused Opamps
Preamp Stage
3.3V Clamp
R113 and R115 were previously 220 Ohm, but not sure why I had them there at all. R113 is now DNP and R115 is 0 ohm
Power
FLIP resistors!!!
1k: Anticipating 20A spikes 205: Anticipating 5A spikes (typical) 32.4: Anticipating 1A spikes
